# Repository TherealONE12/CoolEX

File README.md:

# CooleX

A laptop cooling stand with up to 5 fans and custom PWM control. Built because my laptop kept overheating and commercial cooling pads are overpriced.

And also why not?

## What it is

This is a 3D printed stand with five 80mm fans that sit directly under your laptop. The fans are controlled by a custom PCB that generates PWM signals from a simple analog circuit. Power comes from any USB-C PD charger that can do 12V.

The whole thing costs around $20-25 to build and hopefuly works better than those $60 "gaming" cooling pads on Amazon.

## Project structure

```
hardware/
├── gerbers/
│   └── pwm_Colex_gerbers.zip    ← send this to JLCPCB
├── pwm_Colex.kicad_pro
├── pwm_Colex.kicad_sch           ← schematic
├── pwm_Colex.kicad_pcb           ← PCB layout
├── pwm_Colex.csv                 ← detailed component list
└── BOM.csv                       ← shopping list

mechanical/
├── Part_Studio_1_-_Part_1.step   ← CAD model
└── Part_Studio_1_-_Part_1.stl    ← print this

docs/
└── JOURNAL.md                     ← dev log from the build process
```

## Bill of materials

| Part | Qty | Where | Price | Link |
|------|-----|-------|-------|------|
| Xilence XPF80.R.PWM fans (80mm, 4-pin) | up to 5, recommended 2-4 | Amazon | $16.90 total (For 5)| [Link](https://www.amazon.de/Xilence-XPF80-R-PWM-XF040-PC-L%C3%BCfter-schwarz/dp/B01L6QAX76) |
| PCB (custom) | 1 | JLCPCB | ~$2 | Upload gerbers zip |
| Electronic components | set | Mouser/Digikey | ~$3 | See hardware/pwm_Colex.csv |
| 3D printed stand | 1 | Your printer | ~$2 filament | mechanical/*.stl |

**Total: ~$24**

### Key components on the PCB

- **U1**: NE555DR timer - generates the PWM signal
- **U2**: USB PD chip - asks your charger for 12V
- **Q1-Q5**: MOSFETs - switch each fan on/off
- **D1-D5**: Flyback diodes - protect the MOSFETs from voltage spikes
- **R_POT**: Potentiometer - this is your speed knob

## How it works

**Power:** USB-C PD controller negotiates 12V from whatever charger you plug in

**PWM generation:** The NE555 is wired as an oscillator. Frequency is set by resistors/caps, duty cycle is adjustable with the pot. This gives you smooth fan speed control from silent to full blast.

**Fan control:** Each fan gets constant 12V on the positive rail. The MOSFETs switch the ground connection on/off rapidly (that's the PWM).

## Why I built this

My laptop would hit 95°C and throttle down to like 1.2GHz whenever I tried to compile or game anything. Regular cooling pads either:
- Don't actually blow air WHERE the laptop intakes it
- Use loud DC fans with no speed control
- Cost $40-60 for what's basically fans and plastic

I wanted PWM control (so it can be quiet when idle), proper positioning under the intake vents, and USB-C power. Nothing on the market did all three without being stupidly expensive.

Also I didn't want to use a microcontroller for this. It's literally just "make a square wave with adjustable duty cycle" - the NE555 has been doing that since 1972. Why overcomplicate it?

## Build notes

### PCB

Upload `hardware/gerbers/pwm_Colex_gerbers.zip` to JLCPCB or PCBWay. Default options are fine (2-layer, 1.6mm, HASL finish). Order 5 boards for like $2 + shipping.

Components are all through-hole for easy soldering. Check `hardware/pwm_Colex.csv` for part numbers. Total BOM cost is around $3-4 if you buy from Mouser/Digikey.

### 3D print

Print `mechanical/Part_Studio_1_-_Part_1.stl` in PLA or PETG. Use supports for the overhangs. 20% infill is plenty.

The design has cutouts for USB ports and stuff - these are sized for MY laptop (check JOURNAL.md for which one). You might need to modify them in CAD if your laptop has different port positions.

### Assembly

1. Solder everything to the PCB
2. Drop the five fans into the stand's mounting holes
3. Wire fans to the PCB headers (J2 through J6)
4. Mount the PCB in the little mount on the backside - May or May Not need Hot glue
5. Plug in USB-C and adjust the pot for desired speed

## Usage

Put your laptop on the stand. Plug the USB-C into any PD charger. Turn the pot to adjust fan speed. That's it.

The PD controller will automatically request 12V - if your charger can't do 12V it'll fallback to 9V/5V and the fans will just run slower (still works fine).

## Development

Built for Hack Club's Half Life program. See `docs/JOURNAL.md` for the full build log including all the mistakes I made (there were several).

Main learning: I spent 90 minutes trying to build a sawtooth generator from scratch before realizing the NE555 could just... do that. Read datasheets before reinventing wheels.

## Tools used

- OnShape for CAD (because SolidWorks doesn't run on Linux)
- KiCad 10.0 for PCB design

## Future ideas

- Add a temp sensor so it can auto-adjust based on laptop temperature
- Maybe some LEDs to show fan speed
- Modular mounting holes for different laptop sizes
- USB hub passthrough would be neat

## License

MIT - do whatever you want with it. If you build one, send me a picture!

## Credits

Built by Jakob for Hack Club Half Life

Thanks to asktheman for the sawtooth generator reference image that I ended up not using because the NE555 exists

Built by Jakob. With lots of <3 and some Bugs :)

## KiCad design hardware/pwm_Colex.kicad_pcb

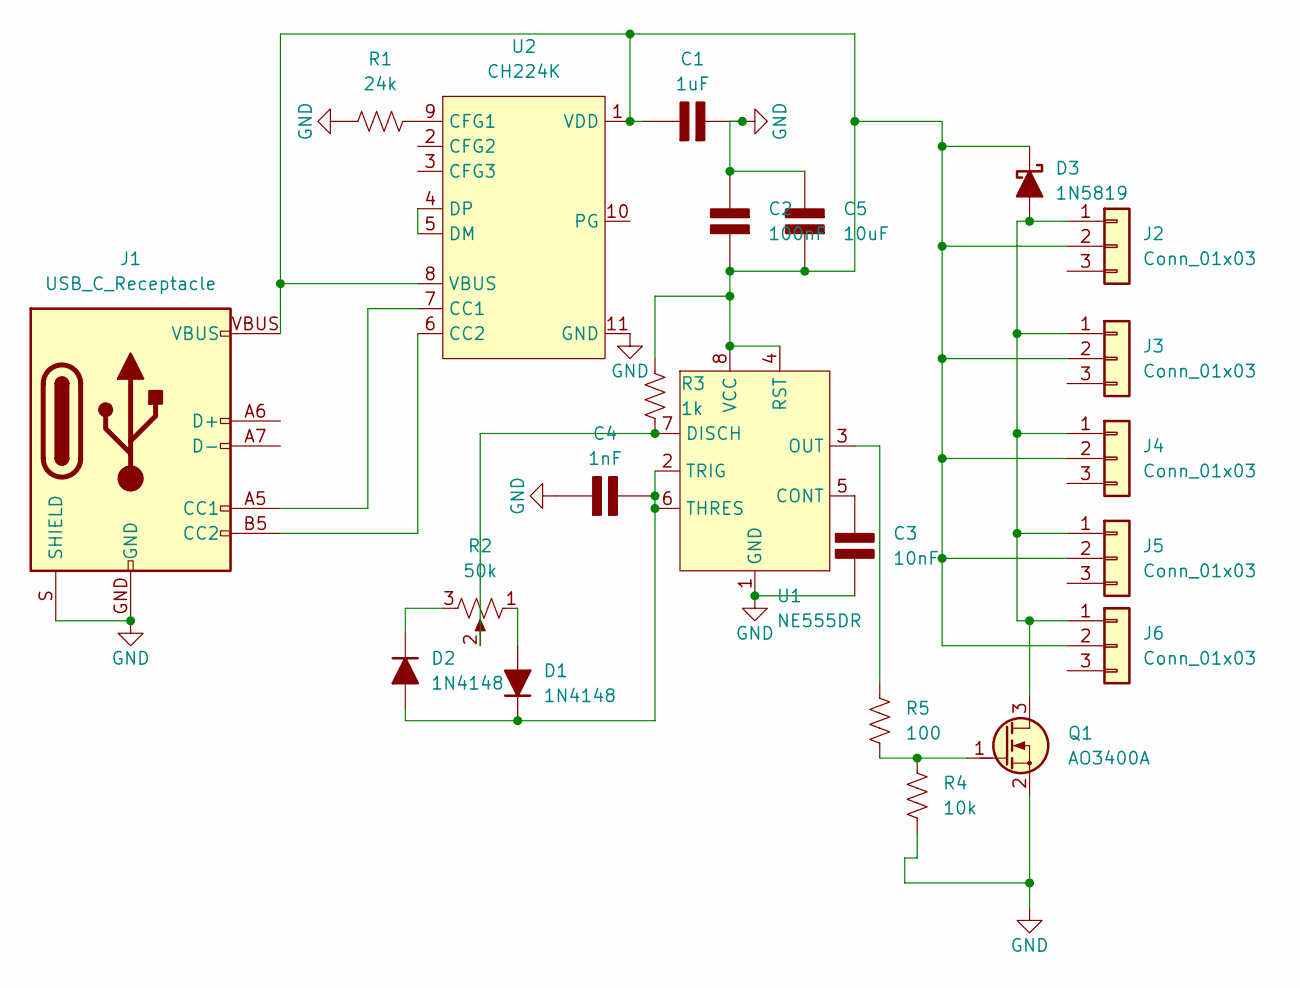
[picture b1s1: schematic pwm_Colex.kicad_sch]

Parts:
C1: 1uF; C_0603; Rating V
C2: 100nF; C_0603; Rating V
C3: 10nF; C_0603; Rating V
C4: 1nF; C_0603; Rating V
C5: 10uF; C_0805; Rating V
D1, D2: 1N4148; D_DO-35_SOD27_P7.62mm_Horizontal
D3: 1N5819; D_DO-41_SOD81_P7.62mm_Horizontal
J1: USB_C_Receptacle; USB-C_16
J2, J3, J4, J5, J6: Conn_01x03; 1x03_P2.54mm; Part Number 1-0301FBV0T
Q1: AO3400A; SOT-23
R1: 24k; R_0603_1608Metric
R2: 50k; Bourns-PDB18
R3: 1k; R_0603_1608Metric
R4: 10k; R_0603_1608Metric
R5: 100; R_0603_1608Metric
U1: NE555DR; SOIC-8_L4.9-W3.9-P1.27-LS6.0-BL; MPN NE555DR; LCSC Part C7593
U2: CH224K; ESSOP-10_L4.9-W3.9-P1.0-LS6.0-TL-EP; MPN CH224K; LCSC Part C970725

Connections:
GND: C1.2 (-), C2.2 (-), C3.2 (-), C4.1 (+), C5.2 (-), J1.GND, J1.S (SHIELD), Q1.2 (S), R1.2, R4.2, U1.1 (GND), U2.11 (GND)
unnamed: C1.1 (+), C2.1 (+), C5.1 (+), D3.1 (K), J1.VBUS, J2.2, J3.2, J4.2, J5.2, J6.2, R3.1, U1.4 (RST), U1.8 (VCC), U2.1 (VDD), U2.8 (VBUS)
unnamed: C3.1 (+), U1.5 (CONT)
unnamed: C4.2 (-), D1.1 (K), D2.2 (A), U1.2 (TRIG), U1.6 (THRES)
unnamed: D1.2 (A), R2.1
unnamed: D2.1 (K), R2.3
unnamed: D3.2 (A), J2.1, J3.1, J4.1, J5.1, J6.1, Q1.3 (D)
unnamed: J1.A5 (CC1), U2.7 (CC1)
unnamed: J1.B5 (CC2), U2.6 (CC2)
unnamed: J1.A6 (D+), J1.B6 (D+)
unnamed: J1.A7 (D-), J1.B7 (D-)
unnamed: Q1.1 (G), R4.1, R5.2
unnamed: R2.2, R3.2, U1.7 (DISCH)
unnamed: R5.1, U1.3 (OUT)
unnamed: R1.1, U2.9 (CFG1)
unnamed: U2.4 (DP), U2.5 (DM)

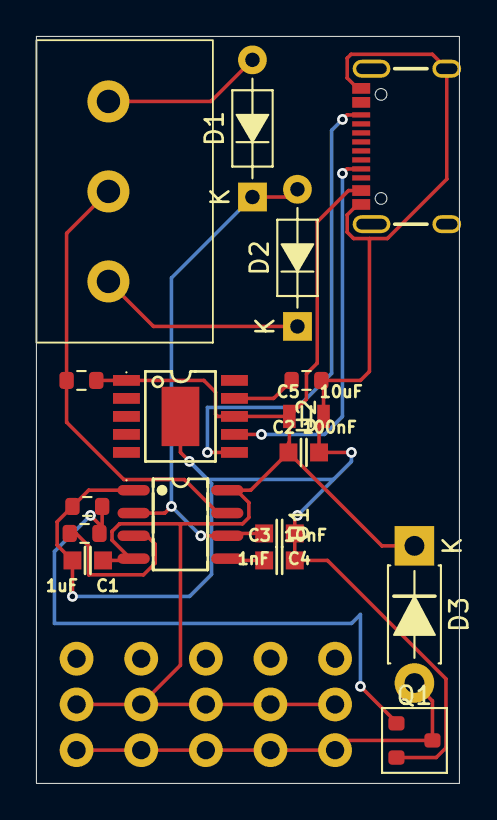
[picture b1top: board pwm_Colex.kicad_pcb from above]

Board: 2 copper layers, 23.5 x 41.5 mm, 22 parts (0 on the bottom side), 16 nets.
